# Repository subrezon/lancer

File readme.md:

# Lancer

The Lancer is a 36-key ortholinear keyboard with a light split and a focus on compact footprint and portability. It is a direct successor to [la_nc](https://github.com/subrezon/la_nc), and is very much inspired by other keyboards like Planck, Lumberjack and Lesovoz.

# Features

- Width of just 11U, the smallest possible with 10 columns and a top-mounted Pro Micro
- More focused thumb row, featuring 6 easily accessible keys
- Powered by a Pro Micro or any other compatible MCU board
- Hotswap sockets in south-facing orientation
- Integrated battery support with a power switch
- Native 3-wire SPI for nice!view support without any bodge wires
- Backwards compatible with oldschool SSD1306 OLEDs (4 leftmost pins of the SPI header)  

# BOM

| Item | Count | Notes |
| :- | :- | :- |
| PCB | 1x | [Gerber file](https://github.com/subrezon/lancer/raw/master/gerbers/lancer-pcb-hotswap/lancer-hotswap-pcb.zip) |
| Top plate | 1x | [Gerber for FR4](https://github.com/subrezon/lancer/raw/master/gerbers/lancer-top-plate/lancer-top-plate.zip), [dxf for other materials](https://github.com/subrezon/lancer/raw/master/dxf/top-plate.dxf) |
| Bottom plate | 1x | [Gerber for FR4](https://github.com/subrezon/lancer/raw/master/gerbers/lancer-bottom-plate/lancer-bottom-plate.zip), [dxf for other materials](https://github.com/subrezon/lancer/raw/master/dxf/bottom-plate.dxf) |
| Pro Micro | 1x | other boards with compatible pinout also work |
| SMD Diodes | 36x | 1N4148W SOD123 |
| MX Hotswap sockets | 36x | Kailh or Gateron |
| Tactile button | 1x | 3x6mm 2-pin button |
| M2 screws | 16x | M2x4 or M2x5, head diameter <5mm |
| M2 standoffs | 8x | 8mm recommended[^1] |
| MX-style switches| 36x | 3-pin or 5-pin |
| 1U MX keycaps | 36x |  |

For wireless operation:

| Item | Count | Notes |
| :- | :- | :- |
| Wireless Pro Micro | 1x | nice!nano, nrfmicro, etc. |
| Rechargeable battery | 1x | 3.7V two-wire battery (eg. 350926) |
| 7-pin SPDT switch | 1x | MSK-12C02 or compatible |

Optionally:

| Item | Count | Notes |
| :- | :- | :- |
| Pro Micro socket | 1-2x | either 1x 24-pin wide or 2x 12-pin single-row |
| Screen | 1x | either nice!view or SSD1306 128x32 OLED |
| Screen socket | 1x | 5-pin |
| Screen cover | 1x | dxf file (coming soon) |

[^1]: 8mm is recommended and will result in equal spacing between top plate, PCB and bottom plate. 7mm can be used for the lowest possible profile, however it is only compatible with Kailh sockets - Gateron sockets slightly thicker.

# Tools

Required:

- Soldering iron/station (+ solder, flux, etc.)
- Screwdriver for the screws
- Side cutters (regular wire cutters will do in a pinch)

Optional (but very recommended):

- Tweezers (preferably reverse ones, for placing diodes & sockets)
- Breadboard (for aligning ProMicro pins)
- Tape (for holding components in place)

Safety measures:

- Fan (for blowing solder fumes away from your face)
- Eye protection (for trimming pins)

# PCB & plates fabrication

Upload the [PCB gerber file](https://github.com/subrezon/lancer/raw/master/gerbers/lancer-pcb-hotswap/lancer-hotswap-pcb.zip) to a PCB manufacturer site like JLCPCB or PCBWay. You can keep settings at default and just pick the color.

If you want FR4 plates, upload [top plate](https://github.com/subrezon/lancer/raw/master/gerbers/lancer-top-plate/lancer-top-plate.zip) and [bottom plate](https://github.com/subrezon/lancer/raw/master/gerbers/lancer-bottom-plate/lancer-bottom-plate.zip) gerbers in the same fashion. If you want plastic or metal plates, use [top plate](https://github.com/subrezon/lancer/raw/master/dxf/top-plate.dxf) and [bottom plate](https://github.com/subrezon/lancer/raw/master/dxf/bottom-plate.dxf) dxf files for cutting.

# Build guide

[Here is a WIP build guide in english](https://github.com/subrezon/lancer/blob/master/docs/build-guide.md). Feel free to submit better photos or translations!

# Firmware

Lancer supports all 3 major firmwares: QMK, ZMK and KMK.

Lancer support in QMK and KMK has been merged into their respective official repositories.

ZMK is user config repository only. Merging into official ZMK repository is currently not planned.

## QMK

The keyboard ID is `subrezon/lancer` in QMK.

Here is an example of flashing the keyboard with the default firmware using the QMK CLI:

```
qmk flash -kb subrezon/lancer -km default
```

If you're unsure what to do with this information, check out the [QMK Documentation](https://docs.qmk.fm/#/) for information on how to get started with QMK.

- I currently do not offer VIA support.
- QMK currently does not support nice!view E-Ink screens.
- If you want to use an SSD1306 OLED, [read this](https://docs.qmk.fm/#/feature_oled_driver) to make it work. The default firmware does not feature any screen support.
- The default firmware is set up for oldschool atmega32u4-based Pro Micros with the caterina bootloader. If you're using an STM or RP2040-based board, you will need to set CONVERT_TO accordingly in your keymap's rules.mk file. [Read this](https://docs.qmk.fm/#/feature_converters?id=converters) for further information.

## ZMK

You can use [this ZMK user config repository](https://github.com/subrezon/zmk-config-lancer) to build ZMK firmware for Lancer. You can:

- Download pre-built firmware from that repository. It is configured for nice!nano v2 and uses the default keymap.
- If you wish to change the keymap and/or use an MCU board other than nice!nano v2, fork that repository and edit the files to suit your needs. The keymap is under `config/boards/shields/lancer/lancer.keymap`.
- If you already have a ZMK user config repository, you may integrate the contents of that repository into your own. Copy the `config/boards/shields/lancer` directory into your repository, then edit your build.yaml to include Lancer:

```
---
include:
  - board: your_other_board
    shield: your_other_shield
  - board: nice_nano_v2
    shield: lancer
```

If you are using an MCU board other than nice!nano v2, change the `nice_nano_v2` board identifier to whatever your board's identifier is. You can find supported boards and their respective identifiers [here](https://zmk.dev/docs/hardware#pro_micro).

If you're new to ZMK, check out the [ZMK documentation](https://zmk.dev/docs) on how to get started.

Note: I might get around to get Lancer officially supported in ZMK main repo, but I feel like Lancer would need to become at least moderately popular first to justify the work. A public user config repo will do for now.

## KMK

To install KMK firmware on your Lancer, follow these steps:

- Download the latest release of [CircuitPython](https://circuitpython.org/downloads) for your MCU board.
- Connect your MCU board to the computer and put it into flashing mode, usually by double-tapping RESET (non-RP2040), or holding BOOT and pressing RESET (RP2040)
- A USB storage device will appear. Copy the `adafruit-circuitpython-*.uf2` you just downloaded onto it and wait. The board will reboot and appear again as a USB storage device named `CIRCUITPY`.
- Download or clone the [KMK Firmware Repository](https://github.com/KMKfw/kmk_firmware). Copy the `kmk` folder and the `boot.py` file onto the MCU.
  - If you use a nice!nano or another MCU board with only 1MB of flash, you will need to [compile the firmware](http://kmkfw.io/docs/Officially_Supported_Microcontrollers#pre-compiling-kmk-for-nicenano) first.
- Delete the `code.py` file, and copy `main.py` and `kb.py` from the `boards/subrezon/lancer` folder.

The `kb.py` file has been set up for nice!nano v2. If you have another MCU board - open the `kb.py` folder and look at line 5. It says:

```
from kmk.quickpin.pro_micro.nice_nano import pinout as pins
```

Change `nice_nano` to match your MCU board. [These ones are supported](https://github.com/KMKfw/kmk_firmware/tree/master/kmk/quickpin/pro_micro).

If yours isn't in the list, you will have to edit the board's pinout yourself.

# Known issues

- The two southmost screws were placed below the middle of switches 4 and 7 of the third row. Unless you're using screws with very small screw heads, they need to be unscrewed before pulling out those two switches. Fixing this would be a plate layout change, so this will likely never be fixed to maintain compatibility between plate/PCB revisions.

# Changelog
- v1.1: first minor revision (latest version, not tested yet)
  - Screen socket moved 1.27mm to the south to make installing a battery underneath the MCU board easier. Hopefully 1.27mm is enough, otherwise it will be move even further away in the next revision.
  - North-facing footprints in thumb cluster, most people install their thumb keycaps upside down, so to maintain south-facingness switches had to be turned 180 degrees as well.
  - Added "ON" and "OFF" silkscreening on the PCB's top side to indicate how the power switch operates.
- v1.0: initial release version (tested, verified working)

# Coming soon

- Acrylic screen cover
- Soldered PCB option
- 3D-printable case options

# Special thanks

- ai03 - for the [MX_V2](https://github.com/ai03-2725/MX_V2) footprint library
- The fabulous mechanical keyboard community - for, well, everything!

# License

This hardware is licensed under the MIT License. You may use it in any way you want.

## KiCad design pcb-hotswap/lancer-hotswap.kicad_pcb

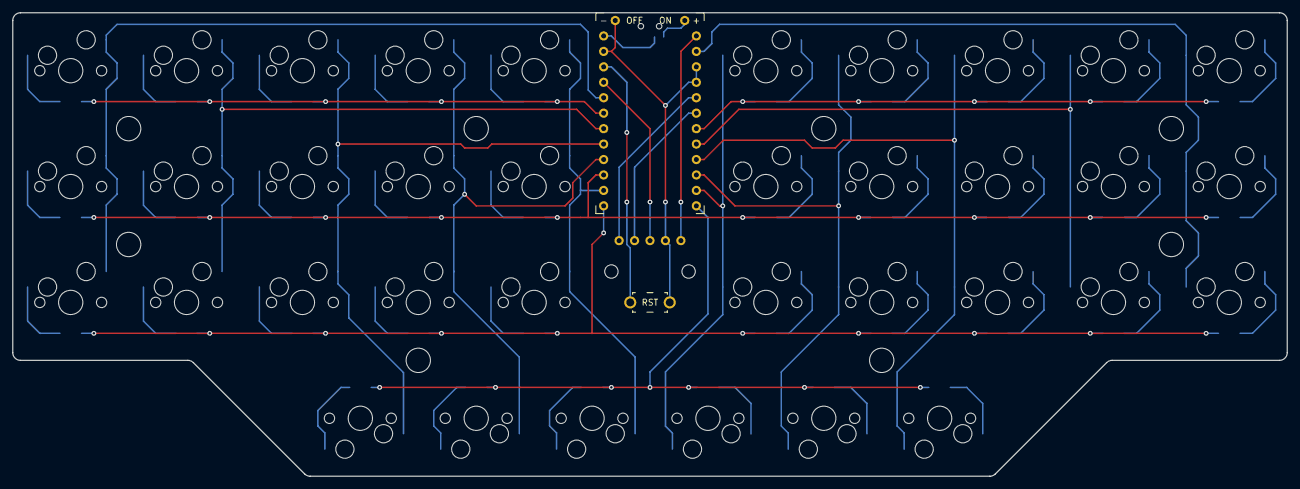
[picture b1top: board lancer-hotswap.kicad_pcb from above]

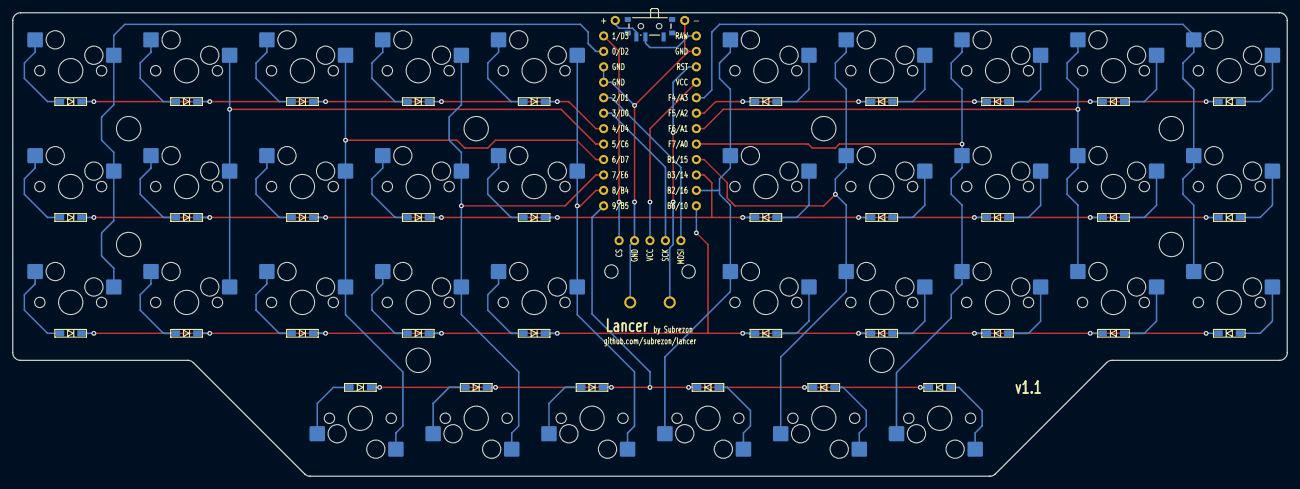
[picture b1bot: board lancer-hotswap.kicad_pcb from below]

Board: 2 copper layers, 209.5 x 76.2 mm, 88 parts (37 on the bottom side), 59 nets.

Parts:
D1, D2, D3, D4, D5, D6, D7, D8, D9, D10, D11, D12, D13, D14, D15, D16, D17, D18, D19, D20, D21, D22, D23, D24, D25, D26, D27, D28, D29, D30, D31, D32, D33, D34, D35, D36: D_Small; Diode_SMD
H1, H2, H3, H4, H5, H6, H7, H8: MountingHole; M2_StandoffHole
H9, H10: MountingHole; M2_ScrewHole
H11, H12: MountingHole_Pad; TH
O1: nice!view
SW1, SW2, SW3, SW4, SW5, SW6, SW7, SW8, SW9, SW10, SW11, SW12, SW13, SW14, SW15, SW16, SW17, SW18, SW19, SW20, SW21, SW22, SW23, SW24, SW25, SW26, SW27, SW28, SW29, SW30, SW31, SW32, SW33, SW34, SW35, SW36: SW_Push; MX-Hotswap-1U
SW37: SW_SPDT; SW_SPDT_PCM12
SW38: SW_Push; SW_Reset
U1: ProMicro_Flipped

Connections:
/BAT+: H12.1, SW37.3 (C)
/C0: SW1.2, SW11.2, SW21.2, U1.20 (A3/F4)
/C1: SW2.2, SW12.2, SW22.2, U1.18 (A1/F6)
/C2: SW3.2, SW13.2, SW23.2, SW31.1, U1.17 (A0/F7)
/C3: SW4.2, SW14.2, SW24.2, SW32.1, U1.16 (15/SCLK/B1)
/C4: SW5.2, SW15.2, SW25.2, SW33.1, U1.14 (16/MOSI/B2)
/C5: SW6.1, SW16.1, SW26.1, SW34.2, U1.11 (B4/8)
/C6: SW7.1, SW17.1, SW27.1, SW35.2, U1.10 (E6/7)
/C7: SW8.1, SW18.1, SW28.1, SW36.2, U1.9 (D7/6)
/C8: SW9.1, SW19.1, SW29.1, U1.8 (C6/5)
/C9: SW10.1, SW20.1, SW30.1, U1.2 (D2/RX1/0)
/CS: O1.5 (CS), U1.1 (D3/TX0/1)
/GND: H11.1, O1.4 (GND), SW38.2, U1.3 (GND), U1.4 (GND), U1.23 (GND)
/R0: D1.1 (K), D2.1 (K), D3.1 (K), D4.1 (K), D5.1 (K), U1.19 (A2/F5)
/R1: D6.1 (K), D7.1 (K), D8.1 (K), D9.1 (K), D10.1 (K), U1.7 (D4/4)
/R2: D11.1 (K), D12.1 (K), D13.1 (K), D14.1 (K), D15.1 (K), D16.1 (K), D17.1 (K), D18.1 (K), D19.1 (K), D20.1 (K), U1.15 (14/MISO/B3)
/R3: D21.1 (K), D22.1 (K), D23.1 (K), D24.1 (K), D25.1 (K), D26.1 (K), D27.1 (K), D28.1 (K), D29.1 (K), D30.1 (K), U1.13 (10/B6)
/R4: D31.1 (K), D32.1 (K), D33.1 (K), D34.1 (K), D35.1 (K), D36.1 (K), U1.12 (B5/9)
/RAW: SW37.2 (B), U1.24 (RAW)
/RST: SW38.1, U1.22 (RST)
/SCL: O1.2 (SCK), U1.6 (D0/SCL/3)
/SDA: O1.1 (MOSI), U1.5 (D1/SDA/2)
/VCC: O1.3 (VCC), U1.21 (VCC)
unnamed: D1.2 (A), SW1.1
unnamed: D2.2 (A), SW2.1
unnamed: D3.2 (A), SW3.1
unnamed: D4.2 (A), SW4.1
unnamed: D5.2 (A), SW5.1
unnamed: D6.2 (A), SW6.2
unnamed: D7.2 (A), SW7.2
unnamed: D8.2 (A), SW8.2
unnamed: D9.2 (A), SW9.2
unnamed: D10.2 (A), SW10.2
unnamed: D11.2 (A), SW11.1
unnamed: D12.2 (A), SW12.1
unnamed: D13.2 (A), SW13.1
unnamed: D14.2 (A), SW14.1
unnamed: D15.2 (A), SW15.1
unnamed: D16.2 (A), SW16.2
unnamed: D17.2 (A), SW17.2
unnamed: D18.2 (A), SW18.2
unnamed: D19.2 (A), SW19.2
unnamed: D20.2 (A), SW20.2
unnamed: D21.2 (A), SW21.1
unnamed: D22.2 (A), SW22.1
unnamed: D23.2 (A), SW23.1
unnamed: D24.2 (A), SW24.1
unnamed: D25.2 (A), SW25.1
unnamed: D26.2 (A), SW26.2
unnamed: D27.2 (A), SW27.2
unnamed: D28.2 (A), SW28.2
unnamed: D29.2 (A), SW29.2
unnamed: D30.2 (A), SW30.2
unnamed: D31.2 (A), SW31.2
unnamed: D32.2 (A), SW32.2
unnamed: D33.2 (A), SW33.2
unnamed: D34.2 (A), SW34.1
unnamed: D35.2 (A), SW35.1
unnamed: D36.2 (A), SW36.1

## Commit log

2023-04-24 v1.0 went to production
2023-05-04 begin release prep
2023-05-04 removed via
2023-05-04 init docs
2023-05-04 cleanup dxf
2023-05-04 added gitignore
2023-05-04 applied gitignore
2023-05-04 typo in build guide
2023-05-04 added changelog
2023-05-05 oled stuff + switched to fancier code segments
2023-05-08 pictures
2023-05-08 added images to readme
2023-05-08 added fab instructions
2023-05-12 zmk init
2023-05-12 zmk awkward wording fix
2023-05-12 more typos
2023-05-19 readme tested zmk
2023-05-30 KMK init
2023-05-31 added known issues
2023-08-09 Update readme firmware section
2023-08-21 v1.1
2023-08-21 v1.1 readme
2023-08-21 v1.1 gerbers
2023-09-04 Update readme.md with file links & official kmk
2023-09-24 Update readme.md official qmk
2023-09-28 Update readme.md link to build guide
2023-09-28 Update build-guide.md improved instructions (no photos yet)
2023-09-28 Update readme.md minor updates
